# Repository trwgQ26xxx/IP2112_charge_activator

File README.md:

# IP2112 charge activator

BC 1.2 & Apple 5V 2A charge activator

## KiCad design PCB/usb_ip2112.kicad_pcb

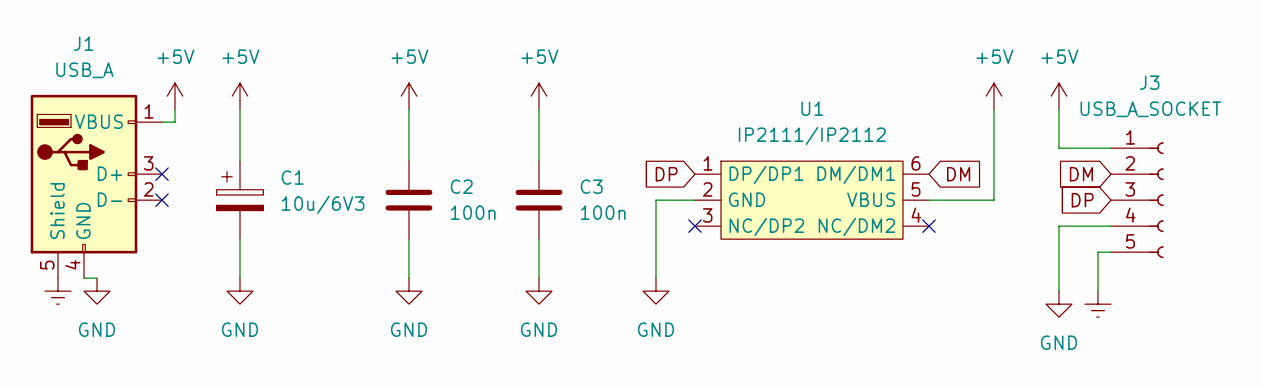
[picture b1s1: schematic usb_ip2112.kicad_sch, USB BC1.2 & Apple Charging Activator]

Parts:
C1: 10u/6V3; CP_EIA-6032-28_Kemet-C_Pad2.25x2.35mm_HandSolder
C2, C3: 100n; C_1206_3216Metric_Pad1.33x1.80mm_HandSolder
J1: USB_A; USB_A_CNCTech_1001-011-01101_Horizontal
J3: USB_A_SOCKET; USB_A_Molex_67643_Horizontal
U1: IP2111/IP2112; TSOT-23-6_HandSoldering

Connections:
+5V: C1.1, C2.1, C3.1, J1.1 (VBUS), J3.1, U1.5 (VBUS)
DM: J3.2, U1.6 (DM/DM1)
DP: J3.3, U1.1 (DP/DP1)
Earth: J1.5 (Shield), J3.5
GND: C1.2, C2.2, C3.2, J1.4 (GND), J3.4, U1.2 (GND)

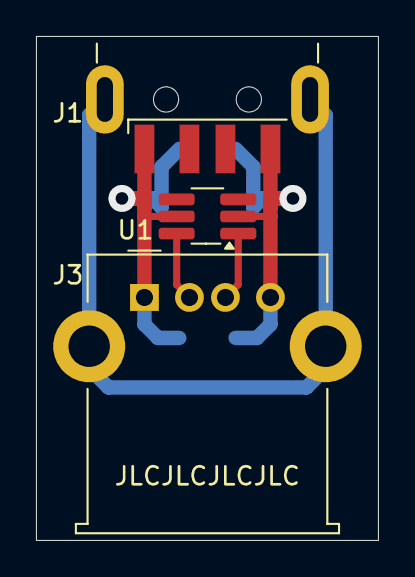
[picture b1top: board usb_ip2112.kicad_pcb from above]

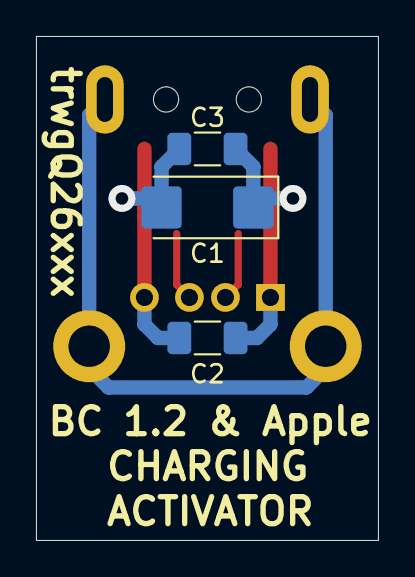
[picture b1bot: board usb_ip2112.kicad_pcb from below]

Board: 2 copper layers, 19.0 x 28.0 mm, 6 parts (3 on the bottom side), 5 nets.

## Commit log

2024-09-16 PCB project added
2025-01-22 Updated .gitignore
2025-02-09 Gitignore updated
